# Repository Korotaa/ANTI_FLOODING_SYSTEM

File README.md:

# Système anti inondation
[https://github.com/Korotaa/ANTI_FLOODING_SYSTEM](https://github.com/Korotaa/ANTI_FLOODING_SYSTEM)
## I. Besoins du système  
1. Détection proactive des niveaux d’eau à l’aide de capteurs robustes.
2. Actionnement automatisé pour évacuation d’eau via une pompe submersible.
3. Signalisation locale et/ou à distance en cas de risque.
4. Résilience énergétique grâce à une batterie de secours.
## II. Design contraintes
1. Fiabilité : Utilisation de capteurs et d’actionneurs éprouvés.
2. Accessibilité : Matériel standard et technologies abordables.
3. Évolutivité : Possibilité d’intégrer des fonctionnalités avancées comme la communication IoT.
##  III. Architecture

## IV. schéma électronique du End-device

## V. PCB
**NB : Le pcb est conçu pour faciliter le prototypage sur PCB double face perforé**

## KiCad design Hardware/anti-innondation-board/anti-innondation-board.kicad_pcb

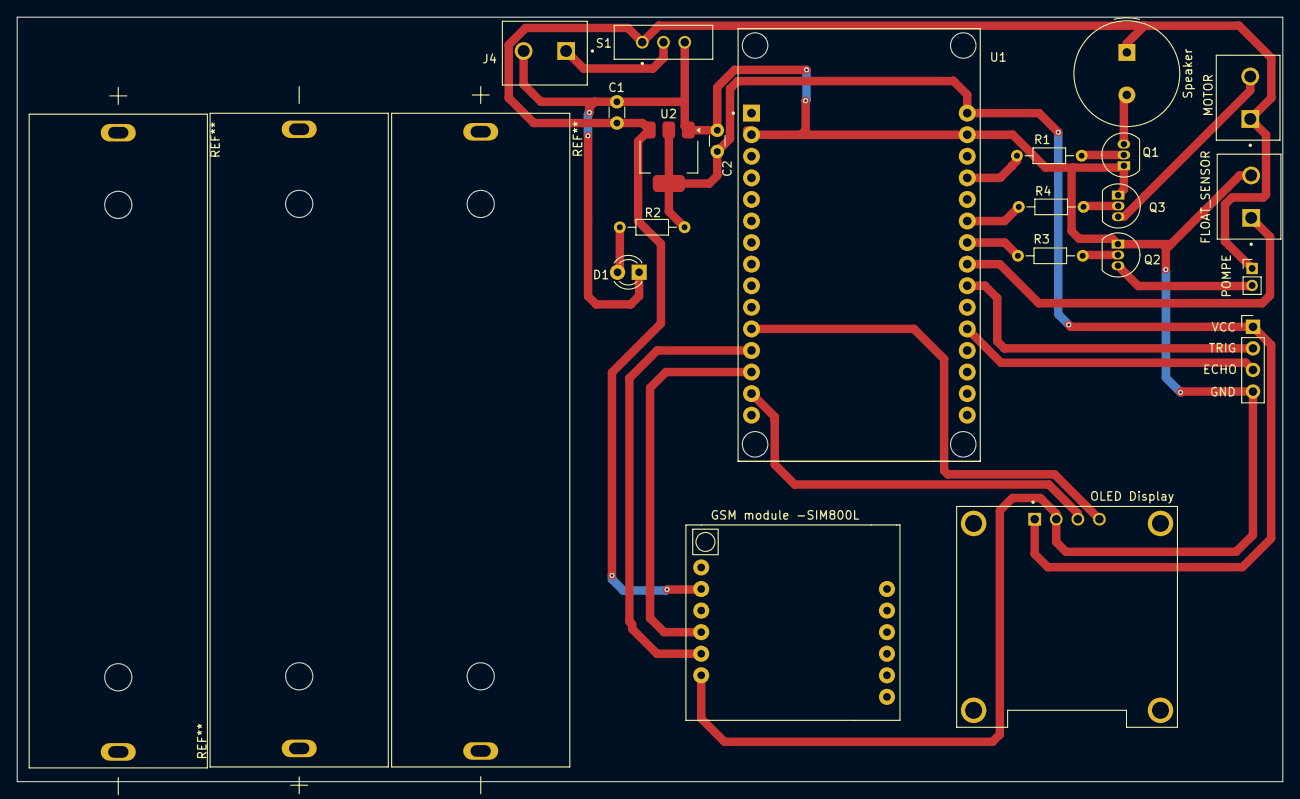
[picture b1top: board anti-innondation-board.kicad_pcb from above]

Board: 2 copper layers, 149.0 x 90.0 mm, 21 parts (0 on the bottom side), 21 nets.

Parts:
C1: 22u; C_Disc_D3.0mm_W1.6mm_P2.50mm
C2: 10u; C_Disc_D3.0mm_W1.6mm_P2.50mm
D1: LED_ALIM; LED_D3.0mm
FLOAT_SENSOR: Float-sensor; HANDSON_KF301-2P
GSM module -SIM800L: SIM800L-CORE; SIM800L
J4: Alimentation; HANDSON_KF301-2P
MOTOR: POMPE; HANDSON_KF301-2P
OLED Display: OLED; MODULE_DM-OLED096-636
POMPE: Motor_vanne; PinHeader_1x02_P2.00mm_Vertical
Q1, Q2, Q3: S8550; TO-92_Inline
R1, R2, R3, R4: 1k; R_Axial_DIN0204_L3.6mm_D1.6mm_P7.62mm_Horizontal
S1: EG1218; SW_EG1218
Speaker: Speaker_Crystal; Buzzer_TDK_PS1240P02BT_D12.2mm_H6.5mm
U1: ESP32-DEVKIT-V1; MODULE_ESP32_DEVKIT_V1
U2: AMS1117-3.3; SOT-223-3_TabPin2
VCC: ultrasonic_sensor; PinHeader_1x04_P2.54mm_Vertical

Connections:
+3.3V: C2.1, OLED Display.1 (GND), R2.1, U1.30 (VIN), U2.2 (VO), VCC.1
/ALARM_GPIO: R1.1, U1.27 (D12)
/ECHO_GPIO: U1.20 (D35), VCC.3
/FLOAT_SENSOR_GPIO: FLOAT_SENSOR.1, U1.23 (D25)
/MOTOR_GPIO: R4.1, U1.25 (D27)
/OLED_SCL: OLED Display.3 (SCL), U1.14 (D22)
/OLED_SDA: OLED Display.4 (SDA), U1.11 (D21)
/POMPE_GPIO: R3.1, U1.24 (D26)
/Q2_COLLECTOR: POMPE.2, Q2.3 (C)
/Q3_COLLECTOR: MOTOR.2, Q3.3 (C)
/SIM800L_RX_GPIO: GSM module -SIM800L.5 (TXD), U1.12 (RX0)
/SIM800L_TX_GPIO: GSM module -SIM800L.4 (RXD), U1.13 (TX0)
/TRIG_GPIO: U1.22 (D33), VCC.2
/Valim: C1.1, GSM module -SIM800L.2 (VCC), MOTOR.1, POMPE.1, S1.1, Speaker.1, U2.3 (VI)
GND: C1.2, C2.2, D1.1 (K), FLOAT_SENSOR.2, GSM module -SIM800L.6 (GND), J4.2, OLED Display.2 (VCC_IN), Q1.1 (E), Q2.1 (E), Q3.1 (E), S1.3, U1.2 (GND), U1.29 (GND__1), U2.1 (GND), VCC.4
unnamed: D1.2 (A), R2.2
unnamed: J4.1, S1.2
unnamed: Q1.2 (B), R1.2
unnamed: Q1.3 (C), Speaker.2
unnamed: Q2.2 (B), R3.2
unnamed: Q3.2 (B), R4.2

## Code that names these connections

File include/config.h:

#include <Adafruit_SSD1306.h>


//LED GPIO
#define LED_GPIO 32

//POMPE GPIO
#define POMPE_GPIO 26

//CAPTEUR DE NIVEAU GPIO
#define FLOAT_SENSOR_GPIO 25

//ULTRASONIC SENSOR GPIOS
#define TRIG_GPIO 33
#define ECHO_GPIO 35

//ALARM GPIO 
#define ALARM_GPIO 23

//MOTOR GPIO
#define MOTOR_GPIO 27

//SIM800L GPIO
#define SIM800L_RX_GPIO 1 
#define SIM800L_TX_GPIO 2
//#define TINY_GSM_MODEM_SIM800L

// Configuration de l'écran OLED
#define SCREEN_WIDTH 128
#define SCREEN_HEIGHT 64
#define OLED_ADDR 0x3C
extern Adafruit_SSD1306 display;

//UART COMMUNICATION SPEED
#define BAUDERATE 115200

//WIFI INFO
extern const char  * SSID;
extern const char * PASSWORD;

//MQTT CONFIG
#define RASPBERRYPI_IP "192.168.11.120"
#define BROKERADDRESS RASPBERRYPI_IP
#define PORT 1883
#define SEND_DATA_TOPIC "/sensors/states"
#define DATA_RECEIVED_TOPIC "/mqttServer/commands"
//#define USERNAME root
//#define PASSWORD root

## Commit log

2025-01-17 software first update
2025-01-17 Software update
2025-01-21 Drivers test
2025-01-27 MQTT Configs
2025-02-21 Hardware part update
2025-02-21 Add files via upload
    images
2025-02-21 Update README.md
    readme update
2025-02-21 Update README.md
    images update
2025-02-21 Hardware update
